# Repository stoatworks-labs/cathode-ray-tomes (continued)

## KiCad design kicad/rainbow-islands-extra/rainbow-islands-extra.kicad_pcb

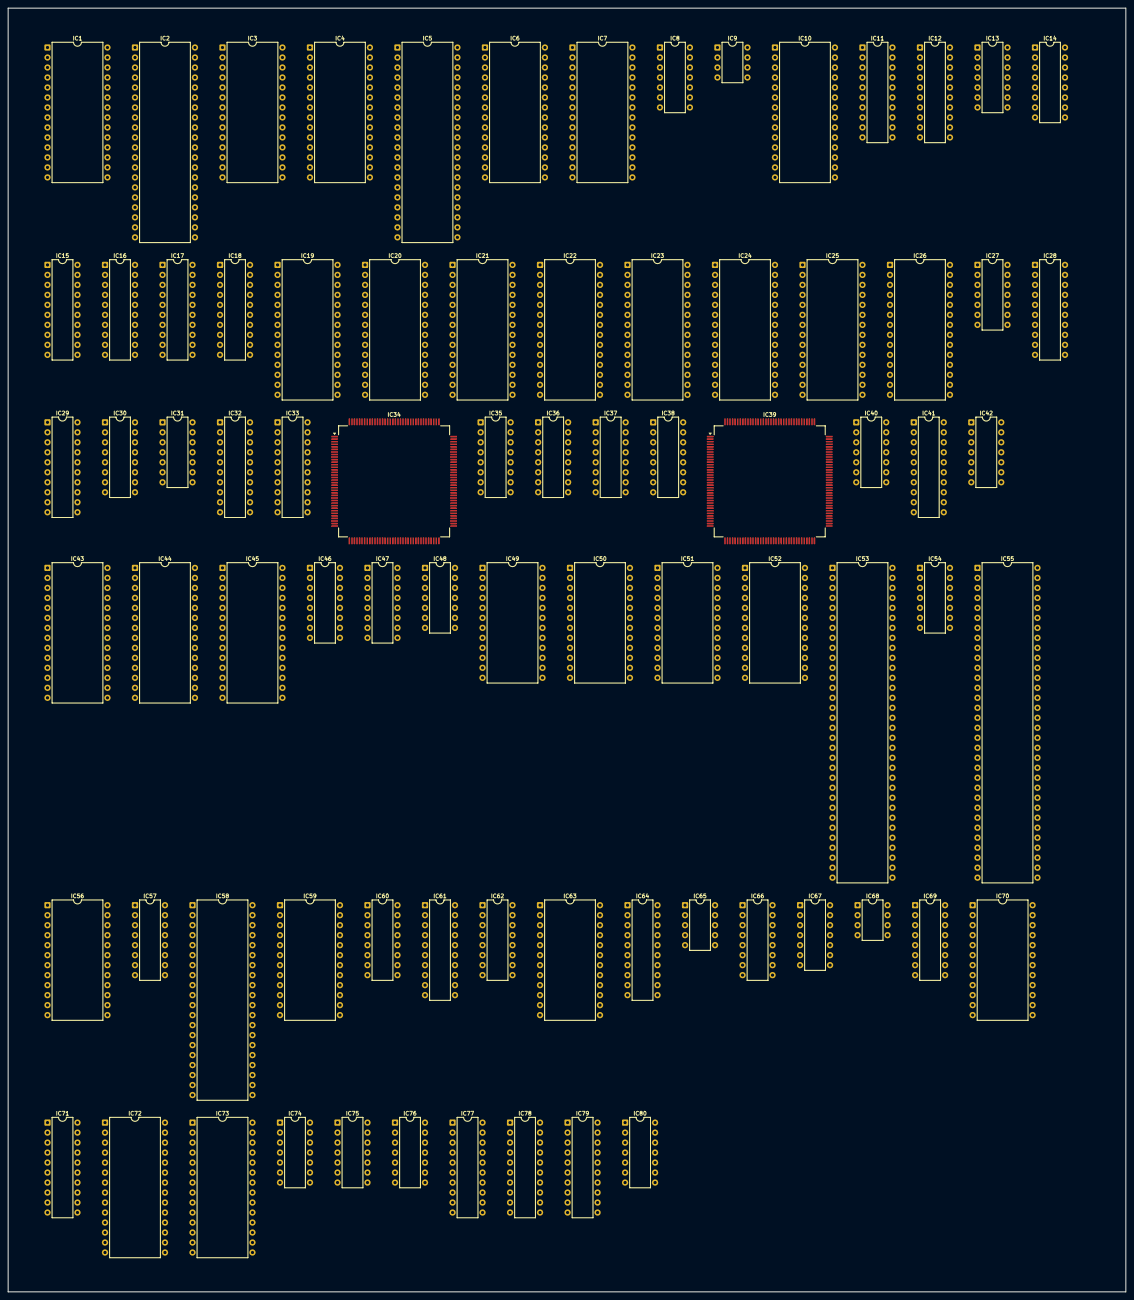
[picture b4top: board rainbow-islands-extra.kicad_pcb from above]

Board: 2 copper layers, 284.1 x 326.3 mm, 80 parts (0 on the bottom side), 445 nets, no tracks yet.

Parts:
IC1, IC6, IC7, IC10, IC19, IC20, IC21, IC22, IC43: 27512; DIP-28_W15.24mm
IC2, IC5: MN234000; DIP-40_W15.24mm
IC3, IC4: 43256-100; DIP-28_W15.24mm
IC8: 74LS393; DIP-14_W7.62mm
IC9: MB3771; DIP-8_W7.62mm
IC11, IC15, IC17, IC28, IC77, IC78, IC79: 74LS244; DIP-20_W7.62mm
IC12, IC16, IC18, IC29: 74LS373; DIP-20_W7.62mm
IC13: 74LS164; DIP-14_W7.62mm
IC14: 74LS139; DIP-16_W7.62mm
IC23, IC24: 23C1000; DIP-28_W15.24mm
IC25, IC26, IC44: MB8464; DIP-28_W15.24mm
IC27, IC40: 74LS08; DIP-14_W7.62mm
IC30: 74F161; DIP-16_W7.62mm
IC31: 74LS32; DIP-14_W7.62mm
IC32, IC61: 74LS273; DIP-20_W7.62mm
IC33, IC41: PAL16L8’; DIP-20_W7.62mm
IC34: PC080SN; PQFP-144_28x28mm_P0.65mm
IC35, IC36, IC47, IC62, IC69: 74LS157; DIP-16_W7.62mm
IC37, IC38: 74LS153; DIP-16_W7.62mm
IC39: PC0900J; PQFP-144_28x28mm_P0.65mm
IC42: 74LS11; DIP-14_W7.62mm
IC45: PC060HA; DIP-28_W15.24mm
IC46: 74LS174; DIP-16_W7.62mm
IC48: 74LS00; DIP-14_W7.62mm
IC49, IC50, IC51, IC52: MCM2018; DIP-24_W15.24mm
IC53: TC0030CMD; DIP-64_W15.24mm
IC54, IC80: 74LS04; DIP-14_W7.62mm
IC55: 68000D; DIP-64_W15.24mm
IC56: PAL20L8; DIP-24_W15.24mm
IC57, IC66: 74LS138; DIP-16_W7.62mm
IC58: Z80CPU; DIP-40_W15.24mm
IC59: YM2151; DIP-24_W15.24mm
IC60: YM3012; DIP-16_W7.62mm
IC63, IC70: MCM2018N35; DIP-24_W15.24mm
IC64, IC71: 74LS245; DIP-20_W7.62mm
IC65: MB3735; DIP-10_W7.62mm
IC67: TL074; DIP-14_W7.62mm
IC68: UPC4556; DIP-8_W7.62mm
IC72: TC0070RGB; DIP-28_W15.24mm
IC73: PC050CM; DIP-28_W15.24mm
IC74: 74LS02; DIP-14_W7.62mm
IC75: 74LS07; DIP-14_W7.62mm
IC76: 74ALS74; DIP-14_W7.62mm

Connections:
-5V: IC67.11, IC68.4
/CPU main/CLK8M: IC30.14, IC45.15, IC55.15
/CPU main/FC0: IC42.11, IC55.28
/CPU main/FC1: IC42.10, IC55.27
/CPU main/FC2: IC42.9, IC55.26
/CPU main/MA19: IC41.5, IC55.47, IC56.6, IC57.6
/CPU main/MA20: IC41.4, IC55.48, IC56.5
/CPU main/MA21: IC41.3, IC55.50, IC56.4
/CPU main/MA22: IC41.2, IC55.51, IC56.3
/CPU main/MA23: IC41.1, IC55.52, IC56.2
/CPU main/MD0: IC20.11, IC22.11, IC24.11, IC26.11, IC32.3, IC34.48, IC39.10, IC45.24, IC53.23, IC55.5, IC64.18, IC77.18, IC78.18, IC79.18
/CPU main/MD1: IC20.12, IC22.12, IC24.12, IC26.12, IC32.18, IC34.93, IC39.11, IC45.23, IC53.24, IC55.4, IC64.17, IC77.3, IC78.3, IC79.3
/CPU main/MD2: IC20.13, IC22.13, IC24.13, IC26.13, IC32.4, IC34.130, IC39.60, IC45.22, IC53.25, IC55.3, IC64.16, IC77.16, IC78.16, IC79.16
/CPU main/MD3: IC20.15, IC22.15, IC24.15, IC26.15, IC32.17, IC34.49, IC39.61, IC45.20, IC53.26, IC55.2, IC64.15, IC77.5, IC78.5, IC79.5
/CPU main/MD4: IC20.16, IC22.16, IC24.16, IC26.16, IC34.94, IC39.103, IC53.27, IC55.1, IC64.14, IC77.14, IC78.14, IC79.14
/CPU main/MD5: IC20.17, IC22.17, IC24.17, IC26.17, IC32.14, IC34.50, IC39.15, IC53.28, IC55.64, IC64.13, IC77.7, IC78.7, IC79.7
/CPU main/MD6: IC20.18, IC22.18, IC24.18, IC26.18, IC32.8, IC34.51, IC39.16, IC53.29, IC55.63, IC64.12, IC77.12, IC78.12, IC79.12
/CPU main/MD7: IC20.19, IC22.19, IC24.19, IC26.19, IC32.13, IC34.52, IC39.66, IC53.30, IC55.62, IC64.11, IC77.9, IC78.9, IC79.9
/CPU main/MD8: IC19.11, IC21.11, IC23.11, IC25.11, IC34.1, IC39.72, IC55.61, IC71.18
/CPU main/MD9: IC19.12, IC21.12, IC23.12, IC25.12, IC34.2, IC39.121, IC55.60, IC71.17
/CPU main/MD10: IC19.13, IC21.13, IC23.13, IC25.13, IC34.3, IC39.117, IC55.59, IC71.16
/CPU main/MD11: IC19.15, IC21.15, IC23.15, IC25.15, IC34.4, IC39.82, IC55.58, IC71.15
/CPU main/MD12: IC19.16, IC21.16, IC23.16, IC25.16, IC34.5, IC39.77, IC55.57, IC71.14
/CPU main/MD13: IC19.17, IC21.17, IC23.17, IC25.17, IC34.6, IC39.76, IC55.56, IC71.13
/CPU main/MD14: IC19.18, IC21.18, IC23.18, IC25.18, IC34.55, IC39.30, IC55.55, IC71.12
/CPU main/MD15: IC19.19, IC21.19, IC23.19, IC25.19, IC34.99, IC39.29, IC55.54, IC71.11
/CPU main/R~W: IC25.27, IC26.27, IC34.10, IC39.55, IC41.11, IC53.33, IC54.9, IC55.9, IC56.14, IC57.3, IC64.1, IC71.1
/CPU main/~CDTACK: IC40.4, IC53.34
/CPU main/~COLRAMBNK: IC32.11, IC57.14
/CPU main/~COLRAMWR: IC41.15, IC47.2
/CPU main/~COLRAM: IC41.16, IC47.1, IC62.1, IC64.19, IC69.1, IC71.19
/CPU main/~COMINT: IC53.3, IC76.11
/CPU main/~COMRES: IC32.2, IC53.22, IC54.5
/CPU main/~COM: IC41.19, IC53.31
/CPU main/~DIPSWA: IC57.11, IC77.1, IC77.19
/CPU main/~DIPSWB: IC57.10, IC78.1, IC78.19
/CPU main/~FC: IC41.13, IC54.2, IC56.1
/CPU main/~HALT: IC55.17, IC75.10
/CPU main/~IO: IC45.28, IC56.21, IC57.5
/CPU main/~MAS: IC41.7, IC55.6, IC56.10
/CPU main/~MDTACK: IC42.5, IC56.22
/CPU main/~MIRQCLR: IC32.19, IC76.13
/CPU main/~MLDS: IC34.60, IC39.3, IC41.9, IC55.8, IC56.13, IC57.4
/CPU main/~MODE: IC41.12, IC53.21
/CPU main/~MUDS: IC34.61, IC39.4, IC41.8, IC55.7, IC56.11
/CPU main/~OBJ: IC39.2, IC56.20
/CPU main/~ODTACK: IC39.131, IC42.4
/CPU main/~PC060RD: IC45.26, IC57.7
/CPU main/~PC060WR: IC45.27, IC57.12
/CPU main/~PLRBTNS: IC57.9, IC79.1, IC79.19
/CPU main/~ROM1CS: IC19.20, IC20.20, IC56.16
/CPU main/~ROM2CS: IC21.20, IC22.20, IC56.17
/CPU main/~ROM3CS: IC23.20, IC24.20, IC56.18
/CPU main/~RST: IC32.1, IC40.11, IC75.9, IC75.11
/CPU main/~RW: IC19.22, IC20.22, IC21.22, IC22.22, IC25.22, IC26.22, IC54.8
/CPU main/~SCCS: IC34.11, IC56.19
/CPU main/~SDTACK: IC34.9, IC42.3
/CPU main/~VPA: IC41.14, IC55.21
/CPU main/~WATCHDOG: IC40.9, IC57.13
/CPU main/~WORAMH: IC25.20, IC41.17
/CPU main/~WORAML: IC26.20, IC41.18
/Color mixer/CB0: IC38.7, IC61.3
/Color mixer/CB1: IC38.9, IC61.4
/Color mixer/CB2: IC37.7, IC61.7
/Color mixer/CB3: IC37.9, IC61.8
/Color mixer/CB4: IC36.12, IC61.13
/Color mixer/CB5: IC36.9, IC61.14
/Color mixer/CB6: IC36.7, IC61.17
/Color mixer/CB7: IC36.4, IC61.18
/Color mixer/CB8: IC35.9, IC46.6
/Color mixer/CB9: IC35.7, IC46.11
/Color mixer/CB10: IC35.4, IC46.13
/Color mixer/CLA0: IC63.8, IC69.12, IC70.8
/Color mixer/CLA1: IC63.7, IC69.9, IC70.7
/Color mixer/CLA2: IC63.6, IC69.7, IC70.6
/Color mixer/CLA3: IC63.5, IC69.4, IC70.5
/Color mixer/CLA4: IC62.12, IC63.4, IC70.4
/Color mixer/CLA5: IC62.9, IC63.3, IC70.3
/Color mixer/CLA6: IC62.7, IC63.2, IC70.2
/Color mixer/CLA7: IC62.4, IC63.1, IC70.1
/Color mixer/CLA8: IC47.12, IC63.23, IC70.23
/Color mixer/CLA9: IC47.9, IC63.22, IC70.22
/Color mixer/CLA10: IC47.7, IC63.19, IC70.19
/Color mixer/CLD0: IC63.9, IC64.2, IC72.3
/Color mixer/CLD1: IC63.10, IC64.3, IC72.4
/Color mixer/CLD2: IC63.11, IC64.4, IC72.5
/Color mixer/CLD3: IC63.13, IC64.5, IC72.6
/Color mixer/CLD4: IC63.14, IC64.6, IC72.7
/Color mixer/CLD5: IC63.15, IC64.7, IC72.8
/Color mixer/CLD6: IC63.16, IC64.8, IC72.9
/Color mixer/CLD7: IC63.17, IC64.9, IC72.10
/Color mixer/CLD8: IC70.9, IC71.2, IC72.11
/Color mixer/CLD9: IC70.10, IC71.3, IC72.12
/Color mixer/CLD10: IC70.11, IC71.4, IC72.13
/Color mixer/CLD11: IC70.13, IC71.5, IC72.14
/Color mixer/CLD12: IC70.14, IC71.6, IC72.15
/Color mixer/CLD13: IC70.15, IC71.7, IC72.16
/Color mixer/CLD14: IC70.16, IC71.8, IC72.17
/Color mixer/CLD15: IC70.17, IC71.9
/Color mixer/CM0: IC61.2, IC69.13
/Color mixer/CM1: IC61.5, IC69.10
/Color mixer/CM2: IC61.6, IC69.6
/Color mixer/CM3: IC61.9, IC69.3
/Color mixer/CM4: IC61.12, IC62.13
/Color mixer/CM5: IC61.15, IC62.10
/Color mixer/CM6: IC61.16, IC62.6
/Color mixer/CM7: IC61.19, IC62.3
/Color mixer/CM8: IC46.7, IC47.13
/Color mixer/CM9: IC46.10, IC47.10
/Color mixer/CM10: IC46.12, IC47.6
/Color mixer/OVCK: IC34.68, IC46.9, IC61.11, IC72.21
/Color mixer/S00: IC34.62, IC38.6
/Color mixer/S01: IC34.63, IC38.10
/Color mixer/S02: IC34.104, IC37.6
/Color mixer/S03: IC34.106, IC37.10
/Color mixer/S10: IC33.4, IC34.133, IC38.5
/Color mixer/S11: IC33.3, IC34.107, IC38.11
/Color mixer/S12: IC33.2, IC34.17, IC37.5
/Color mixer/S13: IC33.1, IC34.108, IC37.11
/Color mixer/SB4: IC34.59, IC36.14
/Color mixer/SB5: IC34.8, IC36.11
/Color mixer/SB6: IC34.58, IC36.5
/Color mixer/SB7: IC34.7, IC36.2
/Color mixer/SB8: IC34.100, IC35.11
/Color mixer/SB9: IC34.57, IC35.5
/Color mixer/SB10: IC34.56, IC35.2
/Color mixer/SEL0: IC33.12, IC34.103, IC37.14, IC38.14
/Color mixer/SEL1: IC33.13, IC35.1, IC36.1, IC37.2, IC38.2
/Color mixer/~CLWE: IC47.4, IC63.21, IC70.21
/Color mixer/~HBL: IC34.12, IC72.20
/Color mixer/~HSYNC: IC13.8, IC33.18, IC34.13, IC39.37
/Color mixer/~VBL: IC8.13, IC34.14, IC72.19, IC80.5
/Color mixer/~VSYNC: IC13.1, IC13.2, IC33.17, IC34.64
/IO/COIN_1_F_INV: IC53.10, IC73.25
/IO/COIN_2_F_INV: IC53.11, IC73.26
/IO/PB2: IC53.12, IC73.14
/IO/PB3: IC53.13, IC73.3
/IO/PB4: IC53.14, IC74.2
/IO/PB5: IC53.15, IC74.11
/IO/PB6: IC53.16, IC74.5
/IO/PB7: IC53.17, IC74.8
/MA1: IC19.10, IC20.10, IC21.10, IC22.10, IC23.10, IC24.10, IC25.10, IC26.10, IC34.117, IC39.99, IC45.25, IC53.35, IC55.29, IC69.14
/MA2: IC19.9, IC20.9, IC21.9, IC22.9, IC23.9, IC24.9, IC25.9, IC26.9, IC34.77, IC39.50, IC53.36, IC55.30, IC69.11
/MA3: IC19.8, IC20.8, IC21.8, IC22.8, IC23.8, IC24.8, IC25.8, IC26.8, IC34.76, IC39.49, IC53.37, IC55.31, IC69.5
/MA4: IC19.7, IC20.7, IC21.7, IC22.7, IC23.7, IC24.7, IC25.7, IC26.7, IC34.30, IC39.94, IC53.38, IC55.32, IC69.2
/MA5: IC19.6, IC20.6, IC21.6, IC22.6, IC23.6, IC24.6, IC25.6, IC26.6, IC34.29, IC39.93, IC53.39, IC55.33, IC62.14
/MA6: IC19.5, IC20.5, IC21.5, IC22.5, IC23.5, IC24.5, IC25.5, IC26.5, IC34.28, IC39.130, IC53.40, IC55.34, IC62.11
/MA7: IC19.4, IC20.4, IC21.4, IC22.4, IC23.4, IC24.4, IC25.4, IC26.4, IC34.27, IC39.126, IC53.41, IC55.35, IC62.5
/MA8: IC19.3, IC20.3, IC21.3, IC22.3, IC23.3, IC24.3, IC25.3, IC26.3, IC34.26, IC39.43, IC53.42, IC55.36, IC62.2
/MA9: IC19.25, IC20.25, IC21.25, IC22.25, IC23.25, IC24.25, IC25.25, IC26.25, IC34.25, IC39.88, IC47.14, IC53.43, IC55.37
/MA10: IC19.24, IC20.24, IC21.24, IC22.24, IC23.24, IC24.24, IC25.24, IC26.24, IC34.24, IC39.42, IC47.11, IC53.44, IC55.38
/MA11: IC19.21, IC20.21, IC21.21, IC22.21, IC23.21, IC24.21, IC25.21, IC26.21, IC34.23, IC39.87, IC47.5, IC53.45, IC55.39
/MA12: IC19.23, IC20.23, IC21.23, IC22.23, IC23.23, IC24.23, IC25.23, IC26.23, IC34.22, IC39.41, IC55.40
/MA13: IC19.2, IC20.2, IC21.2, IC22.2, IC23.2, IC24.2, IC25.2, IC26.2, IC34.21, IC55.41
/MA14: IC19.26, IC20.26, IC21.26, IC22.26, IC23.26, IC24.26, IC34.20, IC40.2, IC55.42
/MA15: IC19.27, IC20.27, IC21.27, IC22.27, IC23.27, IC24.27, IC34.72, IC40.1, IC55.43
/MA16: IC19.1, IC20.1, IC21.1, IC22.1, IC23.1, IC24.1, IC34.71, IC55.44, IC56.9
/MA17: IC23.22, IC24.22, IC34.70, IC55.45, IC56.8, IC57.1
/MA18: IC34.69, IC41.6, IC55.46, IC56.7, IC57.2
/Misc/CLK4M: IC30.13, IC45.14, IC58.6, IC59.24
/Misc/CLK13.343M: IC34.15, IC39.83, IC48.2, IC48.13, IC76.5
/Misc/~RESET: IC9.8, IC40.10, IC40.12, IC45.19
/OUT0: IC33.8, IC38.3, IC38.4, IC39.47
/OUT1: IC33.7, IC38.12, IC38.13, IC39.92
/OUT2: IC33.6, IC37.3, IC37.4, IC39.46
/OUT3: IC33.5, IC37.12, IC37.13, IC39.91
/OUT4: IC36.13, IC39.45
/OUT5: IC36.10, IC39.90
/OUT6: IC36.6, IC39.44
/OUT7: IC36.3, IC39.89
/OUT8: IC32.15, IC35.10
/OUT9: IC32.9, IC35.6
/OUT10: IC32.12, IC35.3
/Sound/SA0: IC43.10, IC44.10, IC45.4, IC58.30, IC59.4
/Sound/SA1: IC43.9, IC44.9, IC58.31
/Sound/SA2: IC43.8, IC44.8, IC58.32
/Sound/SA3: IC43.7, IC44.7, IC58.33
/Sound/SA4: IC43.6, IC44.6, IC58.34
/Sound/SA5: IC43.5, IC44.5, IC58.35
/Sound/SA6: IC43.4, IC44.4, IC58.36
/Sound/SA7: IC43.3, IC44.3, IC58.37
/Sound/SA8: IC43.25, IC44.25, IC58.38
/Sound/SA9: IC43.24, IC44.24, IC58.39
/Sound/SA10: IC43.21, IC44.21, IC58.40
/Sound/SA11: IC43.23, IC44.23, IC58.1
/Sound/SA12: IC43.2, IC44.2, IC58.2, IC66.1
/Sound/SA13: IC43.26, IC58.3, IC66.2
/Sound/SA14: IC31.4, IC58.4, IC66.3
/Sound/SA15: IC31.5, IC43.20, IC58.5, IC66.6
/Sound/SD0: IC43.11, IC44.11, IC45.5, IC58.14, IC59.10
/Sound/SD1: IC43.12, IC44.12, IC45.6, IC58.15, IC59.12
/Sound/SD2: IC43.13, IC44.13, IC45.8, IC58.12, IC59.13
/Sound/SD3: IC43.15, IC44.15, IC45.9, IC58.8, IC59.14
/Sound/SD4: IC43.16, IC44.16, IC58.7, IC59.15
/Sound/SD5: IC43.17, IC44.17, IC58.9, IC59.16
/Sound/SD6: IC43.18, IC44.18, IC58.10, IC59.17
/Sound/SD7: IC43.19, IC44.19, IC58.13, IC59.18
/Sound/~PC6: IC45.1, IC66.13
/Sound/~SINT: IC58.16, IC59.2
/Sound/~SMREQ: IC58.19, IC66.4
/Sound/~SNMI: IC45.12, IC58.17
/Sound/~SRAM: IC44.20, IC66.15
/Sound/~SRD: IC43.22, IC44.22, IC45.3, IC58.21, IC59.6
/Sound/~SRST: IC45.13, IC58.26, IC59.3, IC60.7
/Sound/~SWR: IC44.27, IC45.2, IC58.22, IC59.5
/Sound/~YM2151: IC59.7, IC66.14
/Sprites/OA0: IC39.12, IC49.8, IC50.8, IC51.8, IC52.8
/Sprites/OA1: IC39.13, IC49.7, IC50.7, IC51.7, IC52.7
/Sprites/OA2: IC39.14, IC49.6, IC50.6, IC51.6, IC52.6
/Sprites/OA3: IC39.62, IC49.5, IC50.5, IC51.5, IC52.5
/Sprites/OA4: IC39.63, IC49.4, IC50.4, IC51.4, IC52.4
/Sprites/OA5: IC39.64, IC49.3, IC50.3, IC51.3, IC52.3
/Sprites/OA6: IC39.104, IC49.2, IC50.2, IC51.2, IC52.2
/Sprites/OA7: IC39.106, IC49.1, IC50.1, IC51.1, IC52.1
/Sprites/OA8: IC39.65, IC49.23, IC50.23, IC51.23, IC52.23
/Sprites/OA9: IC39.133, IC49.22, IC50.22, IC51.22, IC52.22
/Sprites/OA10: IC39.107, IC49.19, IC50.19, IC51.19, IC52.19
/Sprites/OAG: IC16.11, IC18.11, IC39.135
/Sprites/OC0: IC17.18, IC18.13, IC39.113
/Sprites/OC1: IC17.16, IC18.14, IC39.134
/Sprites/OC2: IC17.14, IC18.17, IC39.73
/Sprites/OC3: IC17.12, IC18.18, IC39.24
/Sprites/OC4: IC17.9, IC18.8, IC39.116
/Sprites/OC5: IC17.7, IC18.7, IC39.115
/Sprites/OC6: IC17.5, IC18.4, IC39.74
/Sprites/OC7: IC17.3, IC18.3, IC39.25
/Sprites/OC8: IC15.18, IC16.13, IC39.75
/Sprites/OC9: IC15.16, IC16.14, IC39.26
/Sprites/OC10: IC15.14, IC16.17, IC39.27
/Sprites/OC11: IC15.12, IC16.18, IC39.122
/Sprites/OC12: IC15.9, IC16.8, IC39.118
/Sprites/OC13: IC15.7, IC16.7, IC39.81
/Sprites/OC14: IC15.5, IC16.4, IC39.80
/Sprites/OC15: IC15.3, IC16.3, IC39.79
/Sprites/OC16: IC5.32, IC39.78
/Sprites/OC17: IC5.1, IC39.35
/Sprites/OC18: IC14.14, IC39.34
/Sprites/OC19: IC14.13, IC39.33
/Sprites/OCHA0: IC5.9, IC6.10, IC7.10, IC18.12
/Sprites/OCHA1: IC5.8, IC6.9, IC7.9, IC18.15
/Sprites/OCHA2: IC5.7, IC6.8, IC7.8, IC18.16
/Sprites/OCHA3: IC5.6, IC6.7, IC7.7, IC18.19
/Sprites/OCHA4: IC5.5, IC6.6, IC7.6, IC18.9
/Sprites/OCHA5: IC5.4, IC6.5, IC7.5, IC18.6
/Sprites/OCHA6: IC5.3, IC6.4, IC7.4, IC18.5
/Sprites/OCHA7: IC5.2, IC6.3, IC7.3, IC18.2
/Sprites/OCHA8: IC5.40, IC6.25, IC7.25, IC16.12
/Sprites/OCHA9: IC5.39, IC6.24, IC7.24, IC16.15
/Sprites/OCHA10: IC5.38, IC6.21, IC7.21, IC16.16
/Sprites/OCHA11: IC5.37, IC6.23, IC7.23, IC16.19
/Sprites/OCHA12: IC5.36, IC6.2, IC7.2, IC16.9
/Sprites/OCHA13: IC5.35, IC6.26, IC7.26, IC16.6
/Sprites/OCHA14: IC5.34, IC6.27, IC7.27, IC16.5
/Sprites/OCHA15: IC5.33, IC6.1, IC7.1, IC16.2
/Sprites/OCHD0: IC5.13, IC7.11, IC17.2
/Sprites/OCHD1: IC5.15, IC7.12, IC17.4
/Sprites/OCHD2: IC5.17, IC7.13, IC17.6
/Sprites/OCHD3: IC5.19, IC7.15, IC17.8
/Sprites/OCHD4: IC5.22, IC7.16, IC17.11
/Sprites/OCHD5: IC5.24, IC7.17, IC17.13
/Sprites/OCHD6: IC5.26, IC7.18, IC17.15
/Sprites/OCHD7: IC5.28, IC7.19, IC17.17
/Sprites/OCHD8: IC5.14, IC6.11, IC15.2
/Sprites/OCHD9: IC5.16, IC6.12, IC15.4
/Sprites/OCHD10: IC5.18, IC6.13, IC15.6
/Sprites/OCHD11: IC5.20, IC6.15, IC15.8
/Sprites/OCHD12: IC5.23, IC6.16, IC15.11
/Sprites/OCHD13: IC5.25, IC6.17, IC15.13
/Sprites/OCHD14: IC5.27, IC6.18, IC15.15
/Sprites/OCHD15: IC5.29, IC6.19, IC15.17
/Sprites/OD0: IC39.1, IC51.9
/Sprites/OD1: IC39.5, IC51.10
/Sprites/OD2: IC39.52, IC51.11
/Sprites/OD3: IC39.53, IC51.13
/Sprites/OD4: IC39.54, IC51.14
/Sprites/OD5: IC39.56, IC51.15
/Sprites/OD6: IC39.57, IC51.16
/Sprites/OD7: IC39.58, IC51.17
/Sprites/OD8: IC39.59, IC50.9
/Sprites/OD9: IC39.51, IC50.10
/Sprites/OD10: IC39.96, IC50.11
/Sprites/OD11: IC39.97, IC50.13
/Sprites/OD12: IC39.98, IC50.14
/Sprites/OD13: IC39.100, IC50.15
/Sprites/OD14: IC39.95, IC50.16
/Sprites/OD15: IC39.48, IC50.17
/Sprites/OD16: IC39.17, IC52.9
/Sprites/OD17: IC39.108, IC52.10
/Sprites/OD18: IC39.67, IC52.11
/Sprites/OD19: IC39.18, IC52.13
/Sprites/OD20: IC39.109, IC52.14
/Sprites/OD21: IC39.69, IC52.15
/Sprites/OD22: IC39.20, IC52.16
/Sprites/OD23: IC39.112, IC52.17
/Sprites/OD24: IC39.127, IC49.9
/Sprites/OD25: IC39.125, IC49.10
/Sprites/OD26: IC39.124, IC49.11
/Sprites/OD27: IC39.86, IC49.13
/Sprites/OD28: IC39.85, IC49.14
/Sprites/OD29: IC39.40, IC49.15
/Sprites/OD30: IC39.39, IC49.16
/Sprites/OD31: IC39.38, IC49.17
/Sprites/~ORE: IC15.1, IC15.19, IC17.1, IC17.19, IC39.84
/Sprites/~OROM0: IC5.10, IC14.12
/Sprites/~OROM1: IC6.20, IC7.20, IC14.11
/Sprites/~OW0: IC39.6, IC51.21
/Sprites/~OW1: IC39.7, IC50.21
/Sprites/~OW2: IC39.8, IC52.21
/Sprites/~OW3: IC39.9, IC49.21
/Sprites/~VSYNCDL: IC13.13, IC39.36
/Tile layers/SAG: IC12.1, IC12.11, IC29.1, IC29.11, IC34.19
/Tile layers/SC0: IC28.12, IC29.8, IC34.53
/Tile layers/SC1: IC28.9, IC29.13, IC34.54
/Tile layers/SC2: IC28.14, IC29.7, IC34.96
/Tile layers/SC3: IC28.7, IC29.14, IC34.97
/Tile layers/SC4: IC28.16, IC29.4, IC34.95
/Tile layers/SC5: IC28.5, IC29.17, IC34.131
/Tile layers/SC6: IC28.18, IC29.3, IC34.47
/Tile layers/SC7: IC28.3, IC29.18, IC34.92
/Tile layers/SC8: IC11.12, IC12.8, IC34.46
/Tile layers/SC9: IC11.9, IC12.13, IC34.91
/Tile layers/SC10: IC11.14, IC12.7, IC34.90
/Tile layers/SC11: IC11.7, IC12.14, IC34.127
/Tile layers/SC12: IC11.16, IC12.4, IC34.89
/Tile layers/SC13: IC11.5, IC12.17, IC34.125
/Tile layers/SC14: IC11.18, IC12.3, IC34.135
/Tile layers/SC15: IC11.3, IC12.18, IC34.124
/Tile layers/SC16: IC2.32, IC34.86
/Tile layers/SC17: IC2.1, IC34.85
/Tile layers/SC18: IC14.2, IC34.84
/Tile layers/SC19: IC14.3, IC34.122
/Tile layers/SCA0: IC3.10, IC4.10, IC34.33
/Tile layers/SCA1: IC3.9, IC4.9, IC34.32
/Tile layers/SCA2: IC3.8, IC4.8, IC34.31
/Tile layers/SCA3: IC3.7, IC4.7, IC34.80
/Tile layers/SCA4: IC3.6, IC4.6, IC34.79
/Tile layers/SCA5: IC3.5, IC4.5, IC34.78
/Tile layers/SCA6: IC3.4, IC4.4, IC34.118
/Tile layers/SCA7: IC3.3, IC4.3, IC34.75
/Tile layers/SCA8: IC3.25, IC4.25, IC34.116
/Tile layers/SCA9: IC3.24, IC4.24, IC34.115
/Tile layers/SCA10: IC3.21, IC4.21, IC34.74
/Tile layers/SCA11: IC3.23, IC4.23, IC34.134
/Tile layers/SCA12: IC3.2, IC4.2, IC34.73
/Tile layers/SCA13: IC3.26, IC4.26, IC34.113
/Tile layers/SCA14: IC3.1, IC4.1, IC34.112
/Tile layers/SCD0: IC4.11, IC34.40
/Tile layers/SCD1: IC4.12, IC34.39
/Tile layers/SCD2: IC4.13, IC34.38
/Tile layers/SCD3: IC4.15, IC34.37
/Tile layers/SCD4: IC4.16, IC34.36
/Tile layers/SCD5: IC4.17, IC34.83
/Tile layers/SCD6: IC4.18, IC34.82
/Tile layers/SCD7: IC4.19, IC34.121
/Tile layers/SCD8: IC3.11, IC34.41
/Tile layers/SCD9: IC3.12, IC34.42
/Tile layers/SCD10: IC3.13, IC34.87
/Tile layers/SCD11: IC3.15, IC34.43
/Tile layers/SCD12: IC3.16, IC34.88
/Tile layers/SCD13: IC3.17, IC34.126
/Tile layers/SCD14: IC3.18, IC34.44
/Tile layers/SCD15: IC3.19, IC34.45
/Tile layers/SCHA0: IC1.10, IC2.9, IC10.10, IC29.9
/Tile layers/SCHA1: IC1.9, IC2.8, IC10.9, IC29.12
/Tile layers/SCHA2: IC1.8, IC2.7, IC10.8, IC29.6
/Tile layers/SCHA3: IC1.7, IC2.6, IC10.7, IC29.15
/Tile layers/SCHA4: IC1.6, IC2.5, IC10.6, IC29.5
/Tile layers/SCHA5: IC1.5, IC2.4, IC10.5, IC29.16
/Tile layers/SCHA6: IC1.4, IC2.3, IC10.4, IC29.2
/Tile layers/SCHA7: IC1.3, IC2.2, IC10.3, IC29.19
/Tile layers/SCHA8: IC1.25, IC2.40, IC10.25, IC12.9
/Tile layers/SCHA9: IC1.24, IC2.39, IC10.24, IC12.12
/Tile layers/SCHA10: IC1.21, IC2.38, IC10.21, IC12.6
/Tile layers/SCHA11: IC1.23, IC2.37, IC10.23, IC12.15
/Tile layers/SCHA12: IC1.2, IC2.36, IC10.2, IC12.5
/Tile layers/SCHA13: IC1.26, IC2.35, IC10.26, IC12.16
/Tile layers/SCHA14: IC1.27, IC2.34, IC10.27, IC12.2
/Tile layers/SCHA15: IC1.1, IC2.33, IC10.1, IC12.19
/Tile layers/SCHD0: IC2.13, IC10.11, IC28.8
/Tile layers/SCHD1: IC2.15, IC10.12, IC28.11
/Tile layers/SCHD2: IC2.17, IC10.13, IC28.6
/Tile layers/SCHD3: IC2.19, IC10.15, IC28.13
/Tile layers/SCHD4: IC2.22, IC10.16, IC28.4
/Tile layers/SCHD5: IC2.24, IC10.17, IC28.15
/Tile layers/SCHD6: IC2.26, IC10.18, IC28.2
/Tile layers/SCHD7: IC2.28, IC10.19, IC28.17
/Tile layers/SCHD8: IC1.11, IC2.14, IC11.8
/Tile layers/SCHD9: IC1.12, IC2.16, IC11.11
/Tile layers/SCHD10: IC1.13, IC2.18, IC11.6
/Tile layers/SCHD11: IC1.15, IC2.20, IC11.13
/Tile layers/SCHD12: IC1.16, IC2.23, IC11.4
/Tile layers/SCHD13: IC1.17, IC2.25, IC11.15
/Tile layers/SCHD14: IC1.18, IC2.27, IC11.2
/Tile layers/SCHD15: IC1.19, IC2.29, IC11.17
/Tile layers/~SCCE: IC3.20, IC4.20, IC34.81
/Tile layers/~SRL: IC11.1, IC11.19, IC28.1, IC28.19, IC34.18
/Tile layers/~SROM0: IC2.10, IC14.4
/Tile layers/~SROM1: IC1.20, IC10.20, IC14.5
/Tile layers/~WELO: IC4.27, IC34.35
/Tile layers/~WEUP: IC3.27, IC34.34
GND: IC1.14, IC1.22, IC2.11, IC2.12, IC2.30, IC3.14, IC3.22, IC4.14, IC4.22, IC5.11, IC5.12, IC5.30, IC6.14, IC6.22, IC7.14, IC7.22, IC9.2, IC9.4, IC10.14, IC10.22, IC11.10, IC12.10, IC13.7, IC14.1, IC14.15, IC15.10, IC16.1, IC16.10, IC17.10, IC18.1, IC18.10, IC19.14, IC20.14, IC21.14, IC22.14, IC23.14, IC24.14, IC25.14, IC26.14, IC28.10, IC29.10, IC30.3, IC30.4, IC30.5, IC30.6, IC30.8, IC33.10, IC34.101, IC34.105, IC34.110, IC34.114, IC34.119, IC34.123, IC34.128, IC34.132, IC35.15, IC36.15, IC37.1, IC37.15, IC38.1, IC38.15, IC39.101, IC39.105, IC39.110, IC39.114, IC39.119, IC39.123, IC39.128, IC39.132, IC41.10, IC43.14, IC44.14, IC45.7, IC45.10, IC45.11, IC45.18, IC47.15, IC48.4, IC48.5, IC49.12, IC49.20, IC50.12, IC50.20, IC51.12, IC51.20, IC52.12, IC52.20, IC53.32, IC53.63, IC55.16, IC55.53, IC56.12, IC58.29, IC59.1, IC59.11, IC60.3, IC60.8, IC60.16, IC62.15, IC63.12, IC63.18, IC63.20, IC66.5, IC69.15, IC70.12, IC70.18, IC70.20, IC72.18, IC72.28, IC73.1, IC73.6, IC73.11, IC73.15, IC73.22, IC73.24, IC77.10, IC78.10, IC79.10
GNDA: IC65.4, IC68.3, IC68.5
unnamed: IC8.1, IC8.8
unnamed: IC8.6, IC54.11
unnamed: IC25.26, IC26.26, IC40.3
unnamed: IC27.1, IC27.5, IC31.6
unnamed: IC40.5, IC42.6
unnamed: IC40.8, IC54.13
unnamed: IC40.13, IC54.10
unnamed: IC42.8, IC54.1
unnamed: IC27.6, IC43.27
unnamed: IC27.3, IC43.1
unnamed: IC48.6, IC48.9
unnamed: IC48.10, IC48.11
unnamed: IC48.8, IC49.18, IC50.18, IC51.18, IC52.18
unnamed: IC53.20, IC54.4
unnamed: IC53.2, IC73.10
unnamed: IC53.54, IC80.6
unnamed: IC54.6, IC74.3, IC74.6, IC74.9, IC74.12
unnamed: IC55.12, IC55.13, IC55.22
unnamed: IC40.6, IC55.10
unnamed: IC55.23, IC76.8
unnamed: IC55.18, IC75.8
unnamed: IC58.24, IC58.25
unnamed: IC27.2, IC59.8
unnamed: IC27.4, IC59.9
unnamed: IC59.20, IC60.6
unnamed: IC59.19, IC60.5
unnamed: IC59.21, IC60.4
unnamed: IC59.23, IC60.2
unnamed: IC60.14, IC67.2
unnamed: IC60.12, IC67.12
unnamed: IC60.9, IC67.10
unnamed: IC60.10, IC67.5
unnamed: IC60.13, IC67.1
unnamed: IC60.15, IC67.3
unnamed: IC67.6, IC67.7
unnamed: IC67.8, IC67.9
unnamed: IC67.13, IC67.14
unnamed: IC73.17, IC74.1
unnamed: IC73.8, IC74.13
unnamed: IC73.23, IC74.4
unnamed: IC73.20, IC74.10
unnamed: IC76.2, IC76.6
VCC: IC1.28, IC2.21, IC2.31, IC3.28, IC4.28, IC5.21, IC5.31, IC6.28, IC7.28, IC9.5, IC9.6, IC10.28, IC11.20, IC12.20, IC13.9, IC13.14, IC15.20, IC16.20, IC17.20, IC18.20, IC19.28, IC20.28, IC21.28, IC22.28, IC23.28, IC24.28, IC25.28, IC26.28, IC28.20, IC29.20, IC30.1, IC30.7, IC30.9, IC30.10, IC30.16, IC33.20, IC34.102, IC34.109, IC34.111, IC34.120, IC34.129, IC39.19, IC39.21, IC39.22, IC39.23, IC39.68, IC39.70, IC39.71, IC39.102, IC39.111, IC39.120, IC39.129, IC41.20, IC43.28, IC44.26, IC44.28, IC45.21, IC46.1, IC47.3, IC48.1, IC49.24, IC50.24, IC51.24, IC52.24, IC53.1, IC53.19, IC53.53, IC53.64, IC55.14, IC55.24, IC55.25, IC55.49, IC56.24, IC58.11, IC59.22, IC60.1, IC61.1, IC63.24, IC65.7, IC67.4, IC68.8, IC70.24, IC72.1, IC72.23, IC73.5, IC73.9, IC73.21, IC76.1, IC76.4, IC76.10, IC76.12, IC77.20, IC78.20, IC79.20
